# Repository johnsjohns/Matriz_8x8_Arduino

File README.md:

# Matriz_8x8_Arduino
Esquema da Matriz de Led 8x8 com arduino
Feito no Eagle

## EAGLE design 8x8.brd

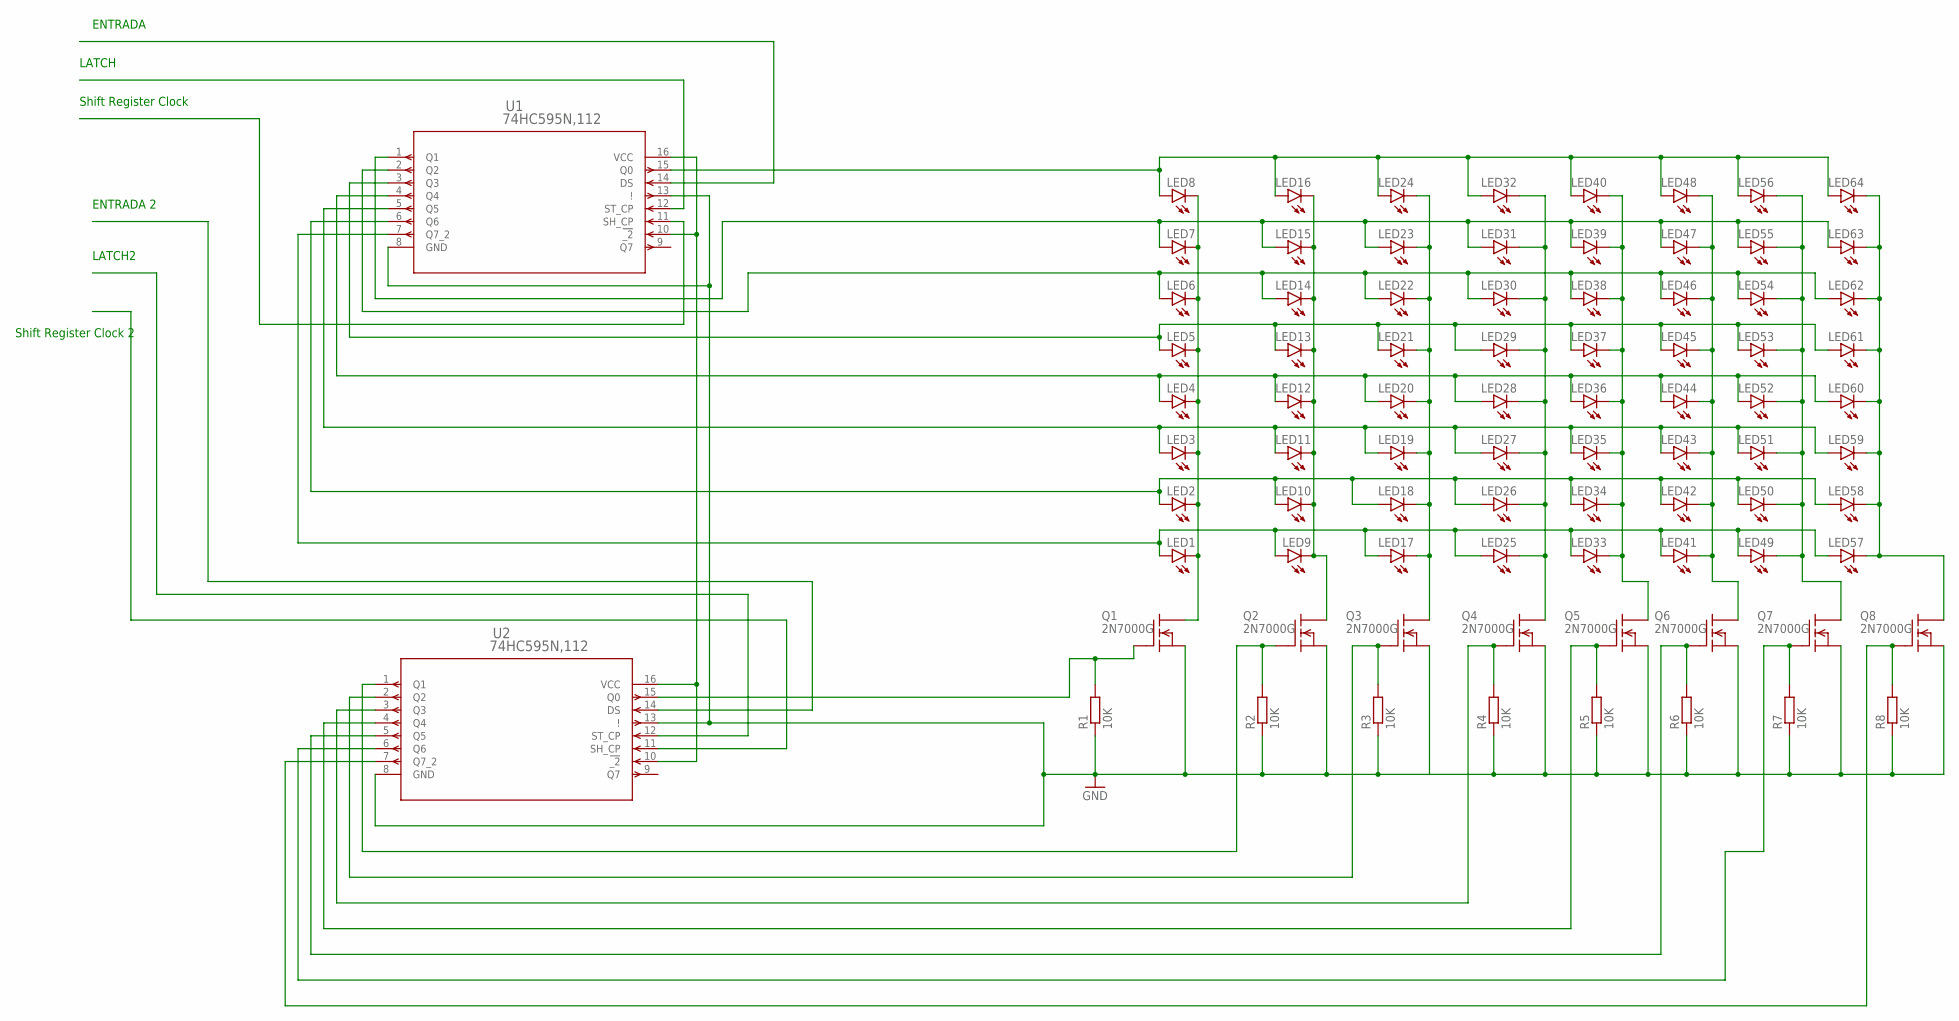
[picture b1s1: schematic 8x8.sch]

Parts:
LED1, LED2, LED3, LED4, LED5, LED6, LED7, LED8, LED9, LED10, LED11, LED12, LED13, LED14, LED15, LED16, LED17, LED18, LED19, LED20, LED21, LED22, LED23, LED24, LED25, LED26, LED27, LED28, LED29, LED30, LED31, LED32, LED33, LED34, LED35, LED36, LED37, LED38, LED39, LED40, LED41, LED42, LED43, LED44, LED45, LED46, LED47, LED48, LED49, LED50, LED51, LED52, LED53, LED54, LED55, LED56, LED57, LED58, LED59, LED60, LED61, LED62, LED63, LED64: LED3MM
Q1, Q2, Q3, Q4, Q5, Q6, Q7, Q8: 2N7000G; TO92-INLINE
R1, R2, R3, R4, R5, R6, R7, R8: 10K; 0204V
U1, U2: 74HC595N,112; SOT38-4_NXP

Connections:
GND: Q1.1 (SRC), Q2.1 (SRC), Q3.1 (SRC), Q4.1 (SRC), Q5.1 (SRC), Q6.1 (SRC), Q7.1 (SRC), Q8.1 (SRC), R1.1, R2.1, R3.1, R4.1, R5.1, R6.1, R7.1, R8.1, U1.8 (GND), U1.13 (!), U2.8 (GND), U2.13 (!)
unnamed: LED1.K (C), LED2.K (C), LED3.K (C), LED4.K (C), LED5.K (C), LED6.K (C), LED7.K (C), LED8.K (C), Q1.3 (DRN)
unnamed: Q1.2 (GATE), R1.2, U2.15 (Q0)
unnamed: Q2.2 (GATE), R2.2, U2.1 (Q1)
unnamed: LED9.K (C), LED10.K (C), LED11.K (C), LED12.K (C), LED13.K (C), LED14.K (C), LED15.K (C), LED16.K (C), Q2.3 (DRN)
unnamed: LED17.K (C), LED18.K (C), LED19.K (C), LED20.K (C), LED21.K (C), LED22.K (C), LED23.K (C), LED24.K (C), Q3.3 (DRN)
unnamed: LED25.K (C), LED26.K (C), LED27.K (C), LED28.K (C), LED29.K (C), LED30.K (C), LED31.K (C), LED32.K (C), Q4.3 (DRN)
unnamed: LED33.K (C), LED34.K (C), LED35.K (C), LED36.K (C), LED37.K (C), LED38.K (C), LED39.K (C), LED40.K (C), Q5.3 (DRN)
unnamed: LED41.K (C), LED42.K (C), LED43.K (C), LED44.K (C), LED45.K (C), LED46.K (C), LED47.K (C), LED48.K (C), Q6.3 (DRN)
unnamed: LED49.K (C), LED50.K (C), LED51.K (C), LED52.K (C), LED53.K (C), LED54.K (C), LED55.K (C), LED56.K (C), Q7.3 (DRN)
unnamed: LED57.K (C), LED58.K (C), LED59.K (C), LED60.K (C), LED61.K (C), LED62.K (C), LED63.K (C), LED64.K (C), Q8.3 (DRN)
unnamed: Q3.2 (GATE), R3.2, U2.2 (Q2)
unnamed: Q4.2 (GATE), R4.2, U2.3 (Q3)
unnamed: Q5.2 (GATE), R5.2, U2.4 (Q4)
unnamed: Q6.2 (GATE), R6.2, U2.5 (Q5)
unnamed: Q8.2 (GATE), R8.2, U2.7 (Q7_2)
unnamed: LED8.A, LED16.A, LED24.A, LED32.A, LED40.A, LED48.A, LED56.A, LED64.A, U1.15 (Q0)
unnamed: LED7.A, LED15.A, LED23.A, LED31.A, LED39.A, LED47.A, LED55.A, LED63.A, U1.1 (Q1)
unnamed: LED6.A, LED14.A, LED22.A, LED30.A, LED38.A, LED46.A, LED54.A, LED62.A, U1.2 (Q2)
unnamed: LED4.A, LED12.A, LED20.A, LED28.A, LED36.A, LED44.A, LED52.A, LED60.A, U1.4 (Q4)
unnamed: LED3.A, LED11.A, LED19.A, LED27.A, LED35.A, LED43.A, LED51.A, LED59.A, U1.5 (Q5)
unnamed: LED2.A, LED10.A, LED18.A, LED26.A, LED34.A, LED42.A, LED50.A, LED58.A, U1.6 (Q6)
unnamed: LED1.A, LED9.A, LED17.A, LED25.A, LED33.A, LED41.A, LED49.A, LED57.A, U1.7 (Q7_2)
unnamed: U1.10 (!_2), U1.16 (VCC), U2.10 (!_2), U2.16 (VCC)
unnamed: LED5.A, LED13.A, LED21.A, LED29.A, LED37.A, LED45.A, LED53.A, LED61.A, U1.3 (Q3)
unnamed: Q7.2 (GATE), R7.2, U2.6 (Q6)

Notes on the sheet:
ENTRADA
ENTRADA 2
Shift Register Clock
Shift Register Clock 2
LATCH2
LATCH

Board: 2 copper layers, 82 parts (0 on the bottom side), 26 nets, no tracks yet.
